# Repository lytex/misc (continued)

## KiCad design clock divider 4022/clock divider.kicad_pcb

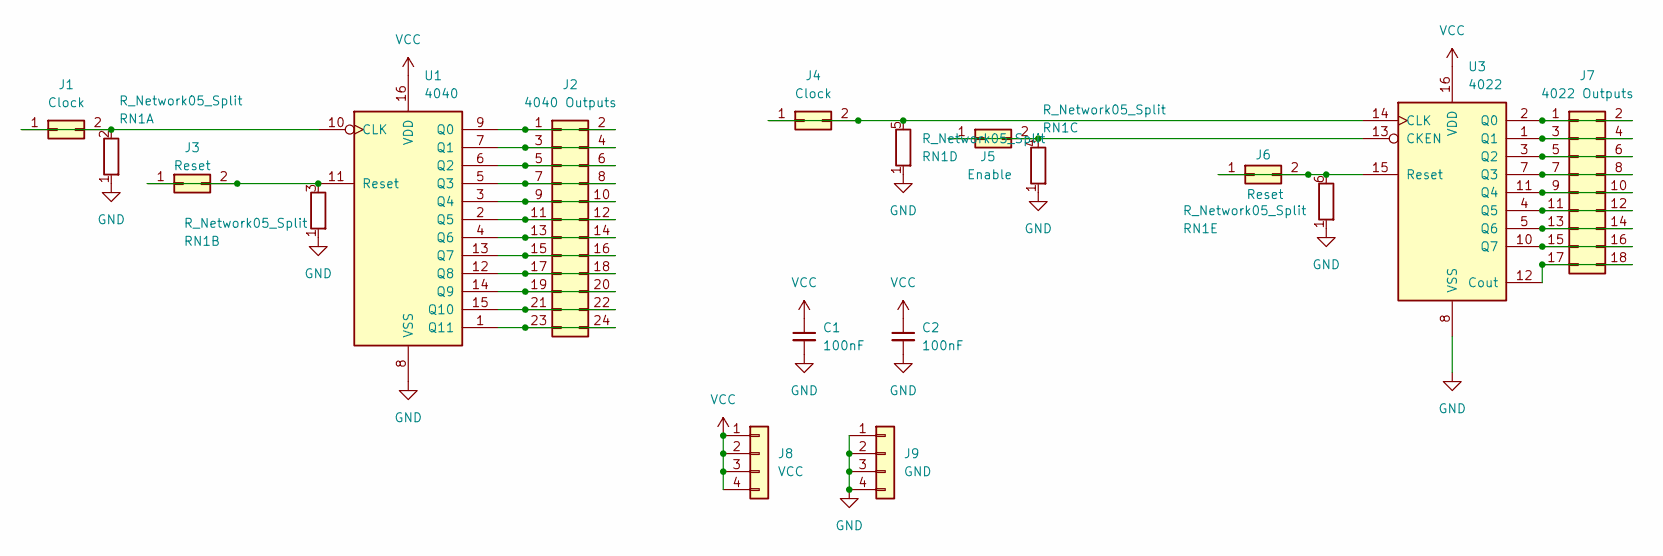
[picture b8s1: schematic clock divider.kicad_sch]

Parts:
C1, C2: 100nF; C_Disc_D3.0mm_W1.6mm_P2.50mm
J1, J4: Clock; PinHeader_2x01_P2.54mm_Vertical
J2: 4040 Outputs; PinHeader_2x12_P2.54mm_Vertical
J3, J6: Reset; PinHeader_2x01_P2.54mm_Vertical
J5: Enable; PinHeader_2x01_P2.54mm_Vertical
J7: 4022 Outputs; PinHeader_2x09_P2.54mm_Vertical
J8: VCC; PinHeader_1x04_P2.54mm_Vertical
J9: GND; PinHeader_1x04_P2.54mm_Vertical
RN1: R_Network05_Split; R_Array_SIP6
U1: 4040; DIP-16_W7.62mm
U3: 4022; DIP-16_W7.62mm

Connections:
GND: C1.2, C2.2, J9.1, J9.2, J9.3, J9.4, RN1.1 (R1), U1.8 (VSS), U3.8 (VSS)
unnamed: J1.1, J1.2, RN1.2 (R1.2), U1.10 (CLK)
unnamed: J2.1, J2.2, U1.9 (Q0)
unnamed: J2.3, J2.4, U1.7 (Q1)
unnamed: J2.5, J2.6, U1.6 (Q2)
unnamed: J2.7, J2.8, U1.5 (Q3)
unnamed: J2.9, J2.10, U1.3 (Q4)
unnamed: J2.11, J2.12, U1.2 (Q5)
unnamed: J2.13, J2.14, U1.4 (Q6)
unnamed: J2.15, J2.16, U1.13 (Q7)
unnamed: J2.17, J2.18, U1.12 (Q8)
unnamed: J2.19, J2.20, U1.14 (Q9)
unnamed: J2.21, J2.22, U1.15 (Q10)
unnamed: J2.23, J2.24, U1.1 (Q11)
unnamed: J3.1, J3.2, RN1.3 (R2.2), U1.11 (Reset)
unnamed: J4.1, J4.2, RN1.5 (R4.2), U3.14 (CLK)
unnamed: J5.1, J5.2, RN1.4 (R3.2), U3.13 (CKEN)
unnamed: J6.1, J6.2, RN1.6 (R5.2), U3.15 (Reset)
unnamed: J7.1, J7.2, U3.2 (Q0)
unnamed: J7.3, J7.4, U3.1 (Q1)
unnamed: J7.5, J7.6, U3.3 (Q2)
unnamed: J7.7, J7.8, U3.7 (Q3)
unnamed: J7.9, J7.10, U3.11 (Q4)
unnamed: J7.11, J7.12, U3.4 (Q5)
unnamed: J7.13, J7.14, U3.5 (Q6)
unnamed: J7.15, J7.16, U3.10 (Q7)
unnamed: J7.17, J7.18, U3.12 (Cout)
VCC: C1.1, C2.1, J8.1, J8.2, J8.3, J8.4, U1.16 (VDD), U3.16 (VDD)

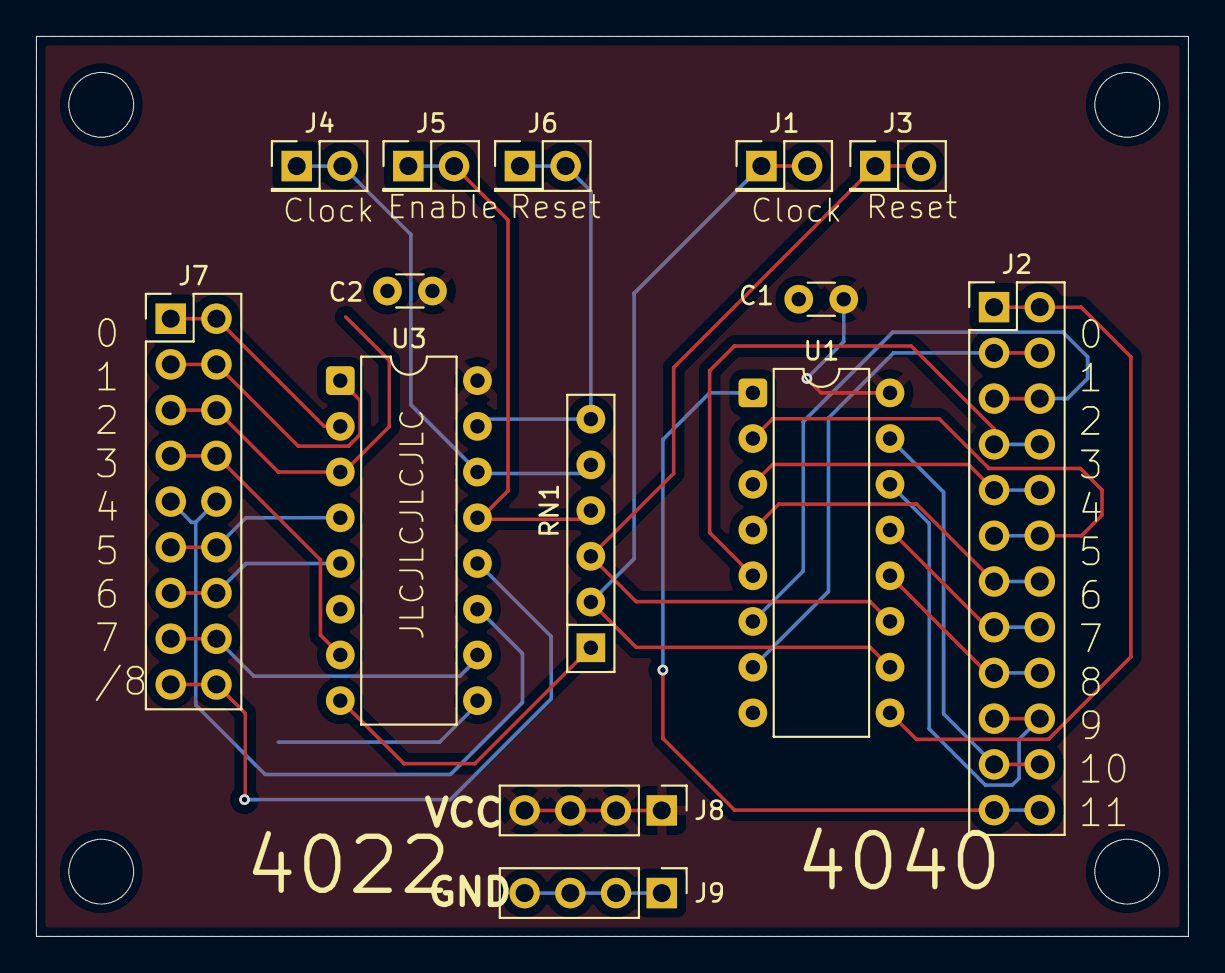
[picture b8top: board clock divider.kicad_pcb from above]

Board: 2 copper layers, 64.0 x 50.0 mm, 14 parts (0 on the bottom side), 28 nets.

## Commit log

2026-01-19 add clock divider
2026-01-19 clock divider with 4022
2026-01-19 add 4067 breakout
2026-01-19 add switchboard
2026-01-19 add baby10 spinoff
2026-02-06 new routing
2026-02-06 remove unused tracks
2026-02-08 cam and LMD files
2026-02-08 rm lck file
2026-02-17 thicker 0.8mm lines
2026-02-17 move to back side, 4 vias
2026-02-18 fix board
2026-03-05 multistate filter
2026-03-05 multistate filter with potentiometer
2026-03-07 multistate filter v2
2026-03-07 multistate filter v3
2026-03-30 40106 monostable
2026-04-05 4050 level shifter tests
2026-04-05 change in gerbers
2026-04-05 more change in gerbers
